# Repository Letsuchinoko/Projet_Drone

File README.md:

# 🛩️ Projet Drone 2025 – Drone autonome piloté par IA & détection de gestes

Projet réalisé à l’IUT de Cachan – Université Paris-Saclay  
**Année universitaire 2024–2025**

---

## 🧠 Objectif du projet

Développer un **drone autonome piloté par reconnaissance gestuelle via IA**, capable de se déplacer dans des **zones difficiles d’accès** pour effectuer des **mesures sonores** (niveau en dB) à proximité d'une enceinte.

### 🔍 Fonctions :
- 🎮 L’utilisateur dirige le drone à l’aide de **gestes manuels**, détectés par la **caméra du drone**.
- 🧠 Une **IA traite les mouvements** pour piloter le drone.
- 📡 Le drone embarque une carte STM32 avec **capteurs GPS et niveau sonore**.
- 📲 Une **application Android** affiche les données récupérées via **Bluetooth**.

---

## 🗂️ Arborescence du dépôt

```
Projet_Drone/
│
├── Carte_Drone/                 # ⚙️ Conception de la carte électronique (KiCad)
│
├── Code/
│   ├── Code_Drone/              # 🎥 Vision embarquée (détection main + OpenCV)
│   ├── Code_API_Drone/          # 📱 App Android pour affichage données capteurs
│   └── Code_general/            # 🔧 (Extensions futures / archives)
│
├── Documents/                   # 📄 Carte mentale, matériel, visuels, images
│   ├── Carte mentale.drawio
│   ├── Liste matériel.pdf
│   └── Projet Drone.png / .gan
│
└── README.md                    # Ce fichier
```

---

## 📌 Sous-projets

### 1. 🎥 Détection de gestes (Vision embarquée – `Code_Drone/`)

Traitement temps réel du **flux vidéo du drone Parrot Bebop 2**, détection d’un **gant rouge** porté par l’utilisateur, IA (TensorFlow) pour classification des gestes.

- Détection couleur (HSV)
- Contrôle du drone par position de la main
- Nettoyage automatique du cache image

👉 [Voir README dédié](./Code/Code_Drone/README.md)

---

### 2. ⚙️ Carte électronique embarquée (`Carte_Drone/`)

Conception et soudure d’une **carte sur KiCad** embarquant plusieurs capteurs :

- Microcontrôleur STM32F303K8T6 (Nucleo-32)
- GPS PMOD
- Capteur de son (DFRobot V2.2)
- Module Bluetooth (ref à confirmer)
- Transmission Bluetooth vers l’app Android

---

### 3. 📱 Application Android (`Code_API_Drone/`)

Développement d’une **application mobile (Android Studio)** permettant de :
- Se connecter en Bluetooth au drone
- Lire les données (GPS + son)
- Afficher ces valeurs en temps réel
- Tester sur plusieurs plateformes (tablette & téléphone)

---

### 4. 🧠 IA pour reconnaissance gestuelle

Utilisation de **TensorFlow**, **HuggingFace** et **Teachable Machine** pour :
- Créer un dataset de mouvements
- Entraîner un modèle de classification
- Prédire des gestes simples
- Contrôler le drone avec ces gestes

---

## 👥 Équipe & responsabilités

| Prénom           | Pseudo GitHub       | Rôle principal                                      | Tâches principales |
|------------------|---------------------|-----------------------------------------------------|---------------------|
| **Bouna**        | `weeduck12`         | Capteurs & instrumentation                          | Configuration capteurs, acquisition GPS, mesure dB, visualisation |
| **Baptiste**     | `Letsuchinoko`      | Carte électronique                                  | Design KiCad, soudure, tests continuité, liaison Bluetooth |
| **Abderrahmane** | `Abderra-boutka`    | Application mobile (API)                            | Dev Android Studio, réception Bluetooth, affichage, tests multiplateforme |
| **Rayan**        | `RayKill`           | IA & pilotage du drone                              | Détection main, reconnaissance de geste, entraînement IA, contrôle drone |

---

## ⚙️ Technologies utilisées

- **Drone** : Parrot Bebop 2 + SDK PyParrot
- **Vision / IA** : Python, OpenCV, ffmpeg, TensorFlow, HuggingFace
- **Carte embarquée** : STM32 Nucleo-32 (C / STMCubeIDE)
- **Mobile** : Android Studio (Java/Kotlin)
- **Électronique** : KiCad
- **Transmission** : Bluetooth

---

## 📅 Avancement

| Module                    | État              |
|---------------------------|-------------------|
| Détection gant + flux     | ✅ Fonctionnel    |
| Carte électronique        | ✅ Fonctionnel    |
| App mobile Android        | ✅ Fonctionnel    |
| Contrôle IA du drone      | ✅ Fonctionnel    |

---

## 🔐 Licence

Ce projet est sous licence **Creative Commons Attribution - NonCommercial 4.0 International (CC BY-NC 4.0)**.  
Vous êtes libre de :
- **Partager** — copier, distribuer et communiquer le matériel par tous moyens et sous tous formats
- **Adapter** — remixer, transformer et créer à partir du matériel

Sous les conditions suivantes :
- **Attribution** — Vous devez créditer le projet, fournir un lien vers la licence, et indiquer si des modifications ont été effectuées.
- **Pas d'utilisation commerciale** — Vous ne pouvez pas faire un usage commercial de ce contenu.

📖 [Consulter la licence complète](https://creativecommons.org/licenses/by-nc/4.0/)

---

## 🏁 Remerciements

Projet encadré par **Mr. Mininger**  
Formation LP MECSE GEII – IUT de Cachan – Université Paris-Saclay – Promo 2025

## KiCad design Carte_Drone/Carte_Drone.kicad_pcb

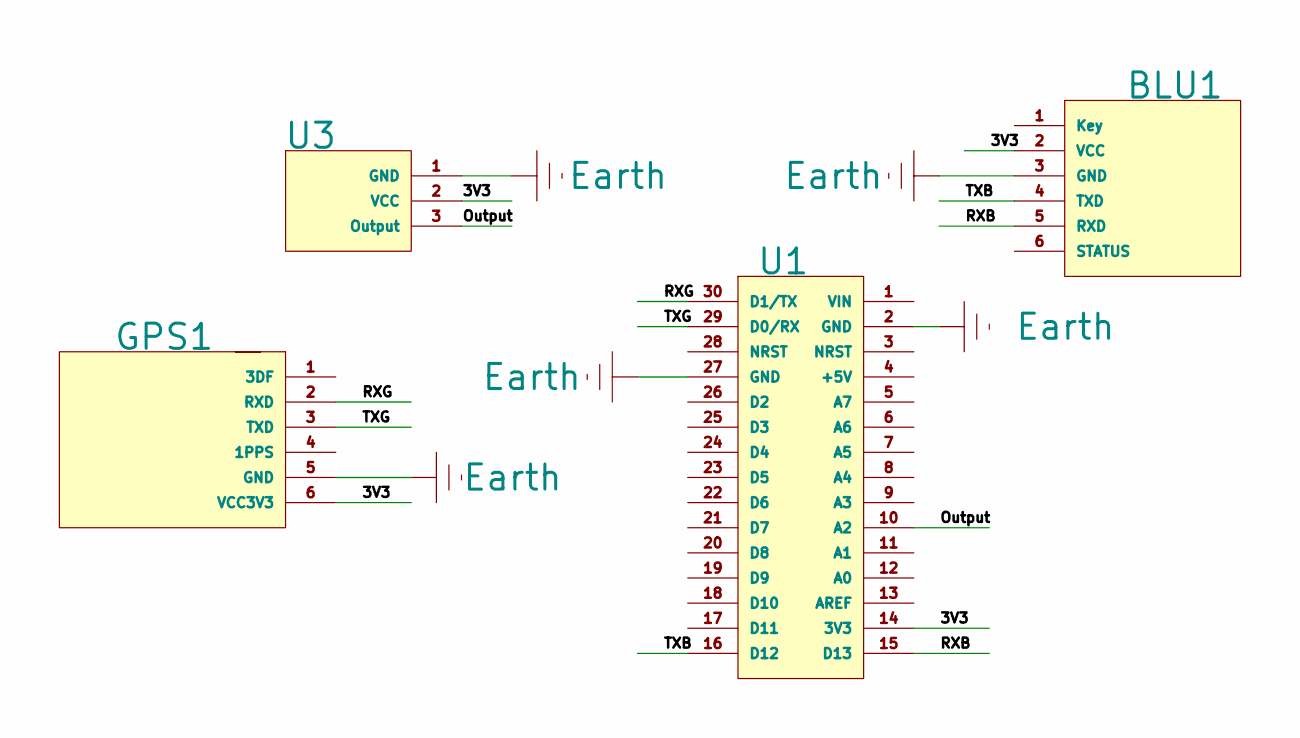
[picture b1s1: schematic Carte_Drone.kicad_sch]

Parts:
BLU1: PinSocket_1x06_P1.27mm_Vertical_2
GPS1: PinSocket_1x06_P1.27mm_Vertical_2
U1: MODULE_NUCLEO-F303K8
U3: PinSocket_1x03_P1.27mm_Vertical_2

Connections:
/3V3: BLU1.2 (VCC), GPS1.6 (VCC3V3), U1.14 (3V3), U3.2 (VCC)
/Output: U1.10 (A2), U3.3 (Output)
/RXB: BLU1.5 (RXD), U1.15 (D13)
/RXG: GPS1.2 (RXD), U1.30 (D1/TX)
/TXB: BLU1.4 (TXD), U1.16 (D12)
/TXG: GPS1.3 (TXD), U1.29 (D0/RX)
Earth: BLU1.3 (GND), GPS1.5 (GND), U1.2 (GND), U1.27 (GND), U3.1 (GND)

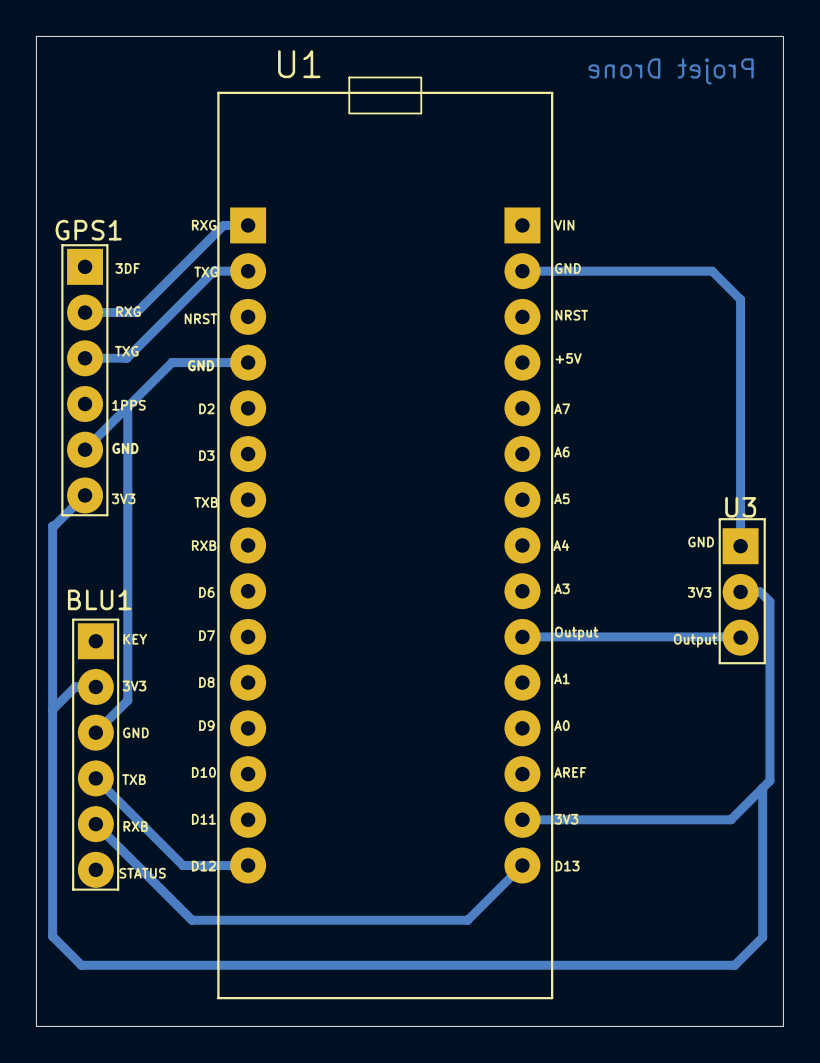
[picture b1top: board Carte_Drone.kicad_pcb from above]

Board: 2 copper layers, 41.5 x 55.0 mm, 4 parts (0 on the bottom side), 7 nets.

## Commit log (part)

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2025-05-12 Ajout et modifications d'empreintes 2
2025-05-12 Ajout connexion capteur son et microcontrôleur
2025-05-12 Ajout d'un composant et de documents
2025-05-12 ajout des fichiers gps et son
2025-05-12 Fin de la création de la carte
2025-05-12 Changement
2025-05-12 ajout de la partie d'abderrahmane
2025-05-12 Ajout label sur la carte
2025-05-13 Ajout des derniers labels
2025-05-13 ajout du projet stm32 prompt a changements voir suppression
2025-05-13 Changement couche label
2025-05-13 Création fichier gerber
2025-05-13 suppression du dossier stm32
2025-05-13 ajout d'un nouveau dossier stm32
2025-05-13 changement de fichier langue stm32
2025-05-13 raccourcis kicad générés
2025-05-13 Ajout code test
2025-05-20 Organisation et fusion fichier perçage
2025-05-20 V1 Camera Drone
2025-05-20 V1 test
2025-05-20 V1 testsss
2025-05-20 suppression a nouveau du dossier stm
2025-05-20 ajout de la bonne configuration de projet pour la carte stm32
2025-05-20 V1 Code proto
2025-05-20 Test Capture Gant
2025-05-20 Changement code Test_Flux_Video
2025-05-20 Nouvelles versions codes
2025-05-20 New Code Versions
2025-05-20 Version Code new
2025-05-20 V1 tests flux video
2025-05-20 New version
2025-05-20 Code V1 Officiel
2025-05-20 Déplacement Codes
2025-05-20 Tests code detection+flux
2025-05-20 Déplacement fichiers codes
2025-05-20 V1 detection live
2025-05-20 New version Code Detection_Live
2025-05-20 New readme file
2025-05-20 Readme update
2025-05-20 Modification typon
2025-05-20 Création images
2025-05-20 New versions
2025-05-20 New version code capture gant
2025-05-20 Création carte mentale
2025-05-20 Readme Updates
2025-05-20 ÃÃcommit update app
2025-05-20 Changement empreinte 1
2025-05-21 Changement empreinte 2 et modification typon
2025-05-21 New API
2025-05-21 Ajout code préparation IA
2025-05-21 Alignement empreinte et génération fichiers gerber
2025-05-21 Update code prototypage data analysis
2025-05-21 New version code data analysis
2025-05-21 Mise à jour code
2025-05-21 code update
2025-05-21 Update Fix crash Prototypage data analysis
2025-05-21 Update Code
2025-05-21 images
2025-05-21 Test
2025-05-21 images 2
2025-05-21 avancements code drone
2025-05-21 Image deplacées
2025-05-21 Update API
2025-05-21 drone gps
2025-05-22 New readme
2025-05-22 suppression images
2025-05-22 code fonctionnel de la recuperation de trame gps
2025-05-22 modif main
2025-05-22 mise à jour capture schéma
2025-05-22 Code modifié prototype
2025-05-22 Prototypage New flux video
2025-05-22 Test Prototypage
2025-05-22 Bebop.sdp modifications
2025-05-22 Tests code
2025-05-22 New code test
2025-05-22 Code test
2025-05-22 Update code test
2025-05-22 Test 4612 Prototype Flux
2025-05-22 code terminal
2025-05-22 test code
2025-05-22 nouveau fichier
2025-05-27 ajout de la conversion analogique numerique
2025-05-30 transmission de valeurs capteur son
2025-06-03 ajout fichier de backup kicad non suivi
2025-06-03 Update code analysis
2025-06-03 Changement typon et empreinte
2025-06-03 code terminal 1
2025-06-03 New code for data analysis
2025-06-03 Update code data analysis
2025-06-03 Test new version
2025-06-03 Update new code
2025-06-03 ajout pins GPIO configurables
2025-06-03 corrections config bluetooth
2025-06-05 Update code Anaysis data
2025-06-05 Test code avec RAM
2025-06-05 New test code
2025-06-05 Code update fullram
2025-06-05 log 2
2025-06-05 Test code analysis
2025-06-05 log 3
2025-06-05 Updates codes
2025-06-05 Update version
2025-06-05 log 4
2025-06-05 log 5
2025-06-05 Update fullram code
2025-06-05 modif typon 2 création Sysml
2025-06-05 Update codes
2025-06-05 log 6
2025-06-05 Code no DroneVision
2025-06-05 Update code fullram
2025-06-05 log 7
2025-06-05 New code updated Analysis
2025-06-05 Diagramme des exigences
2025-06-05 log 8
2025-06-05 log 8 + diagramme des utilisateurs
2025-06-05 log 9
2025-06-05 log 10 + debut GANTT
2025-06-05 Update code prototype 1 fonctionnel
2025-06-05 log 11
2025-06-05 Prototype 2
2025-06-05 Update code Prototype 2
2025-06-05 log 312 + diagramme de bloc
2025-06-05 Ajouts connection bluethoot avec l'appareil, grace à l'affichage des appreils disponible à proximité
2025-06-05 Retour ancienne version
2025-06-05 corrections
2025-06-09 last update
2025-06-10 log 13
2025-06-10 suppression
2025-06-10 log 14
2025-06-10 Update code suite
2025-06-10 Test code version ancienne
2025-06-10 Gantt
2025-06-10 Ancienne version stable
2025-06-10 log 15
2025-06-10 Update readme code drone
2025-06-10 Renommage Gantt+préparation Gantt final
2025-06-10 Del logs
2025-06-10 code fonctionnel todo: son a regler.Trame a parser
2025-06-10 Test new update
2025-06-10 Version antérieur code
2025-06-10 log 16
2025-06-10 Test new code
2025-06-12 log 17
2025-06-12 Update code commandes
2025-06-12 Update code test new version
2025-06-12 V1 Code
2025-06-12 Test code sans commandes
2025-06-12 log 18
2025-06-12 Retour V1 fonctionnel
2025-06-12 V1 avec IA, premier tests
2025-06-12 Test code pour tenserflow
2025-06-12 Update test code
2025-06-12 Update V1 IA
2025-06-12 test tenserflow
2025-06-12 log 19
2025-06-12 mise à jour
2025-06-12 Update code V1 IA
2025-06-12 Save fix V1 IA
2025-06-12 Fix IA file
2025-06-12 log 20 +IA
2025-06-12 ajout du precedent code
2025-06-16 Update code IA
2025-06-16 Revert "Update code IA"
    This reverts commit 1d3dafc0be2aceebceaf855afd7b9860f7a33910.
2025-06-16 Revert "Update code IA"
    This reverts commit 34bdf4055302d234d0c91fe33fff9d78f10eed79.
2025-06-16 Fix code IA - gestion
2025-06-16 Update code IA - Tests Seuils
2025-06-16 log 21 + IA
2025-06-16 Update IA Code Tests
2025-06-16 Update code debug IA
2025-06-16 log 22 + IA
2025-06-16 Tests debug modèle IA
2025-06-16 log 23+IA
2025-06-16 log 24 + IA
2025-06-18 Code Update Debug IA
2025-06-18 log 25 + ia
2025-06-18 Fix error code
2025-06-18 log 26 + AI
2025-06-18 code fonctionnel, todo : son a regler
2025-06-18 Update Code IA Protoype
2025-06-18 log 27 + courbe
2025-06-18 Update code IA prototype 2
2025-06-18 log 28 + courbe ia
2025-06-18 réadaptation code
2025-06-18 Code IA prototype 3 - Update 50 frames/gestes
2025-06-18 log 29 + IA courbe
2025-06-18 code
2025-06-23 test changement parsing
2025-06-23 commit necessaire
2025-06-23 Update fix 50 Echantillons IA
2025-06-23 suppression dossier non necessaire
2025-06-23 log 30 + ia + images + courbe
2025-06-23 V1 Pilotage AI Prototype
2025-06-23 Remove unnecessary logs
2025-06-23 Thresholds Update
2025-06-23 log 31 + powerpoint
2025-06-23 Fix predict_position + threshold
2025-06-23 log 32
2025-06-23 Test IA prototype Pilotage 2
2025-06-23 Update code with logs
2025-06-23 log 33
2025-06-23 Test debug
2025-06-23 Test debug IA
2025-06-23 Test V1 IA Pilotage
2025-06-23 Update Code IA Pilotage
2025-06-23 visualisation de la position du drone sur google maps (test)
2025-06-23 changement code ajout parsing semi complet
2025-06-23 Synoptique
2025-06-23 parsing finalise
2025-06-24 mise à jour synoptique
2025-06-24 Fix error Code IA
2025-06-24 modification
2025-06-24 log 34
2025-06-24 V1 Updated Code IA
2025-06-24 Changement délai entrainement
2025-06-24 Update detection IA
2025-06-24 Amélioration Capture Gant IA
2025-06-24 Update et tests capture gant IA
2025-06-24 log 35
2025-06-24 affichage donné gps et son dans les differents fragments
2025-06-24 Update code IA tests
2025-06-24 todo: conversion gps decimales
2025-06-25 corrections : valeurs gps etranges
2025-06-25 Update IA
2025-06-25 code pc iut
2025-06-25 Comparation code IA
2025-06-25 Tests versions IA
2025-06-25 Amélioration contour gant
2025-06-25 Test amélioration capture gant
2025-06-25 Old version test
2025-06-25 Update Positions IA
2025-06-25 todo annuler la conversion
2025-06-25 avancement: essaie d'affichage position du drone sur la carte de google maps
2025-06-25 capture
2025-06-25 Test seuils qualité
2025-06-25 log 36 +ia + courbes+matrices
2025-06-25 v finale
2025-06-26 Test Epochs/Echantillons upgrade
2025-06-26 Update plage couleurs
2025-06-26 Test plage couleurs
2025-06-26 Test couleurs
2025-06-26 rendu final
2025-06-26 Tests V1 Semi-Finale
2025-06-26 log37+ia+coubes+matrices
2025-06-26 Add commande arret
2025-06-26 Update délai commandes
2025-06-26 Update test
2025-06-26 log 37
2025-06-26 gant version finale
2025-06-26 No limites Test
2025-06-26 mise à jour documents
2025-06-27 mise à jour présentation
2025-06-28 dernière modifications , rendu final
2025-06-28 Refactor code structure for improved readability and maintainability
2025-06-28 Remove obsolete image files from the repository
2025-06-28 Code Final Commenté
2025-06-28 mise à jour rapport
